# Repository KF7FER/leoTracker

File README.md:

leoTracker
==========

Small AVR-based standalone APRS Tracker for [Trackuino](http://www.trackuino.org/)

This board was designed to be fairly inexpensive (BOM is $50 depending upon power source), small (1.25"x2.85"), light (under 17g depending upon configuration), and offer some features typically not available on other trackers.  

A ready to fly leoTracker (sans antenna) often weighs less than the power supply needed for other commercial APRS trackers.

Features include:

- ublox MAX-7/8 GPS w/ chip antenna
- Multiple Power options including boost converter (2xAA operation)
- Atmel (AVR) 32u4 Processor (same as in the Arduino Leonardo - hence the "leo")
- On-board USB for easy firmware updates
- microSD socket for data logging/board configuration
- DS18b20 temperature sensor (and connection for off-board sensor)
- NiceRF SA818 2m radio module (frequency agile; multiple power levels)

The leoTracker ONE
------------------

This is a test version of the leoTracker with an on-board single "AA" battery.  Testing has shown that despite running the SA818 just outside of the published specifications, the leoTracker will function correctly for 11+ hours.  It also has a few changes to support soldering the antenna directly to the PCB to reduce overall payload weight.

Status
--------

I just submitted the Revision "J" boards to fabrication and will post the results here.  The primary changes were a slightly changed footprint for the SA818; I changed the crystal footprint to match the part specified in the BOM (which actually has better low-temperature performance); and I cleaned up the silkscreen for fabrication.

Since those are very minor changes I don't expect any problems but I'll update this as soon as I get the boards back in my hands.

Firmware
--------
The firmware is available at [github.com/KF7FER/trackuino](https://github.com/KF7FER/trackuino). It is modified from the [John Boiles](https://github.com/johnboiles/trackuino) port in order to support the different pin mappings used on the leoTracker (as well as support of additional hardware).  This is, of course, based on EA5HAV's original [Trackuino](https://code.google.com/p/trackuino/)

Changes to the firmware include:

- Support for the ublox MAX-6/7/8 (switch to flight mode; use low power mode when possible)
- Support for the on-board microSD card (still a work in progress)
- Support for the Dallas DS18b20 temperature sensors (two are supported)
- Added support for the NiceRF SA818 radio module

I/O Pin Usage
--------
Here is a document listing I/O pin usage for the different leoTracker versions

Powering the leoTracker
--------

The board may be powered by the following methods:

- Add-on TI TPS61202 Boost converter ([Pololu U1V10F3](http://www.pololu.com/product/2563)) on JP1
- 2xAA Boost converter board (files available w/ leoTracker)
- 3.3v LDO board (this is for vehicle/aircraft use) for 5-20v power sources
- A LiPoly/Solar board is currently under development

Bill of Materials
-----------------

The Bill of Materials is a bit out of date but should be fairly close

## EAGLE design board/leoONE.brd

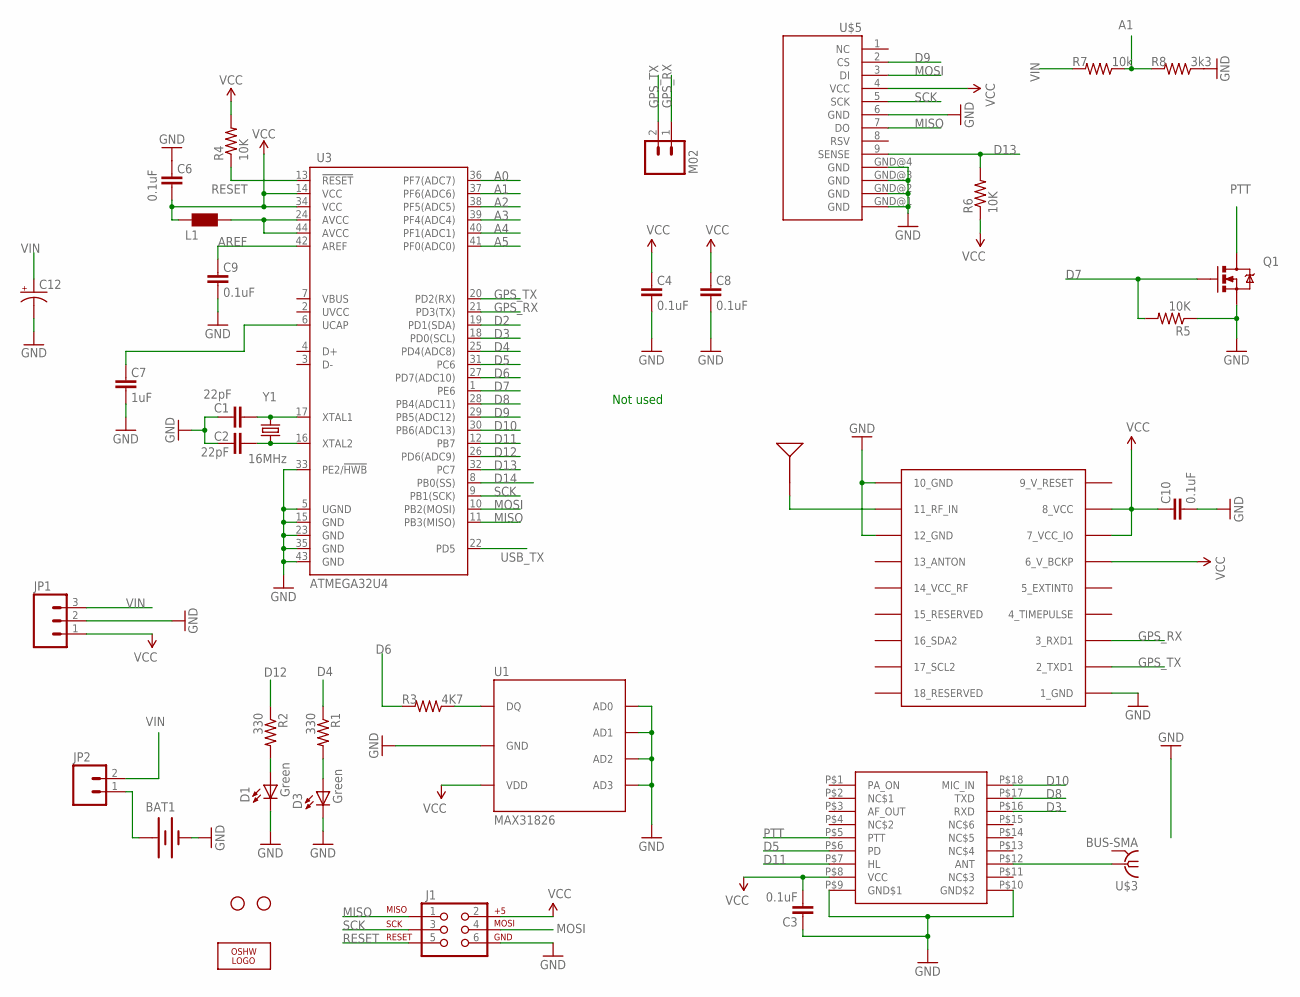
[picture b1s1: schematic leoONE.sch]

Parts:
BAT1: BATTERYAA; BATTERY-AA
C1, C2: 22pF; 0805
C3, C6, C9, C10: 0.1uF; 0805
C4, C8: 0.1uF; 0402-CAP
C7: 1uF; 0805
C12: CPOL-US153CLV-0405; 153CLV-0405
D1, D3: Green; LED-0603
J1: AVR_SPI_PRG_6PTH; 2X3
JP1: M03LOCK; 1X03_LOCK
JP2: M02LOCK; 1X02_LOCK
L1: MH2029-300Y; 0805
LOGO1: OSHW_LOGO_8MILX0200-NT; OSHW_8X200_NOTEXT
Q1: MOSFET-NCHANNELSMD; SOT23-3
R1, R2: 330; 0805
R3: 4K7; 0805
R4, R5, R6: 10K; 0805
R7: 10k; 0805
R8: 3k3; 0805
STANDOFF1, STANDOFF2: STAND-OFFTIGHT; STAND-OFF-TIGHT
U1: MAX31826; UMAX8
U3: ATMEGA32U4; SPARKFUN-DIGITALIC_TQFP44
U$1: ANTENNA2SMD6; ANTENNA-CHIP6
U$2: UBLOX_MAX
U$3: BUS-SMA
U$5: MICROSD_PI; MICROSD_PP
U$7: SA818
U$8: M02
Y1: 16MHz; ABRACON_ABM3_CRYSTAL

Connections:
9_V_RESET: U$2.9_V_RESET
A0: U3.36 (PF7(ADC7))
A1: R7.1, R8.2, U3.37 (PF6(ADC6))
A2: U3.38 (PF5(ADC5))
A3: U3.39 (PF4(ADC4))
A4: U3.40 (PF1(ADC1))
A5: U3.41 (PF0(ADC0))
AREF: C9.2, U3.42 (AREF)
D2: U3.19 (PD1(SDA))
D3: U3.18 (PD0(SCL)), U$7.P$16 (RXD)
D4: R1.1, U3.25 (PD4(ADC8))
D5: U3.31 (PC6), U$7.P$6 (PD)
D6: R3.2, U3.27 (PD7(ADC10))
D7: Q1.1 (G), R5.2, U3.1 (PE6)
D8: U3.28 (PB4(ADC11)), U$7.P$17 (TXD)
D9: U3.29 (PB5(ADC12)), U$5.2 (CS)
D10: U3.30 (PB6(ADC13)), U$7.P$18 (MIC_IN)
D11: U3.12 (PB7), U$7.P$7 (HL)
D12: R2.1, U3.26 (PD6(ADC9))
D13: R6.2, U3.32 (PC7), U$5.9 (SENSE)
D14: U3.8 (PB0(SS))
GND: BAT1.GND@1 (-), C1.2, C2.2, C3.2, C4.1, C6.2, C7.1, C8.1, C9.1, C10.1, C12.-, D1.C, D3.C, J1.6, JP1.2, Q1.2 (S), R5.1, R8.1, U1.4 (GND), U1.5 (AD0), U1.6 (AD1), U1.7 (AD2), U1.8 (AD3), U3.5 (UGND), U3.15 (GND), U3.23 (GND), U3.33 (PE2/!HWB), U3.35 (GND), U3.43 (GND), U$2.1_GND, U$2.10_GND, U$2.12_GND, U$3.2 (GND), U$3.3 (GND), U$3.4 (GND), U$3.5 (GND), U$5.6 (GND), U$5.GND@1 (GND), U$5.GND@2 (GND), U$5.GND@3 (GND), U$5.GND@4 (GND), U$7.P$9 (GND$1), U$7.P$10 (GND$2)
GPS_RX: U3.21 (PD3(TX)), U$2.3_RXD1, U$8.1
GPS_TX: U3.20 (PD2(RX)), U$2.2_TXD1, U$8.2
MISO: J1.1, U3.11 (PB3(MISO)), U$5.7 (DO)
MOSI: J1.4, U3.10 (PB2(MOSI)), U$5.3 (DI)
unnamed: C2.1, U3.16 (XTAL2), Y1.P$1 (1)
unnamed: C1.1, U3.17 (XTAL1), Y1.P$2 (2)
unnamed: R3.1, U1.2 (DQ)
unnamed: C7.2, U3.6 (UCAP)
unnamed: D3.A, R1.2
unnamed: BAT1.PWR@1 (+), JP2.1
unnamed: D1.A, R2.2
unnamed: U$1.1, U$2.11_RF_IN
unnamed: L1.2, U3.24 (AVCC), U3.44 (AVCC)
unnamed: U$3.1, U$7.P$12 (ANT)
PTT: Q1.3 (D), U$7.P$5 (PTT)
RESET: J1.5, R4.1, U3.13 (!RESET)
SCK: J1.3, U3.9 (PB1(SCK)), U$5.5 (SCK)
USB_TX: U3.22 (PD5)
VCC: C3.1, C4.2, C6.1, C8.2, C10.2, J1.2, JP1.1, L1.1, R4.2, R6.1, U1.1 (VDD), U3.14 (VCC), U3.34 (VCC), U$2.6_V_BCKP, U$2.7_VCC_IO, U$2.8_VCC, U$5.4 (VCC), U$7.P$8 (VCC)
VIN: C12.+, JP1.3, JP2.2, R7.2

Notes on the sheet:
Not used

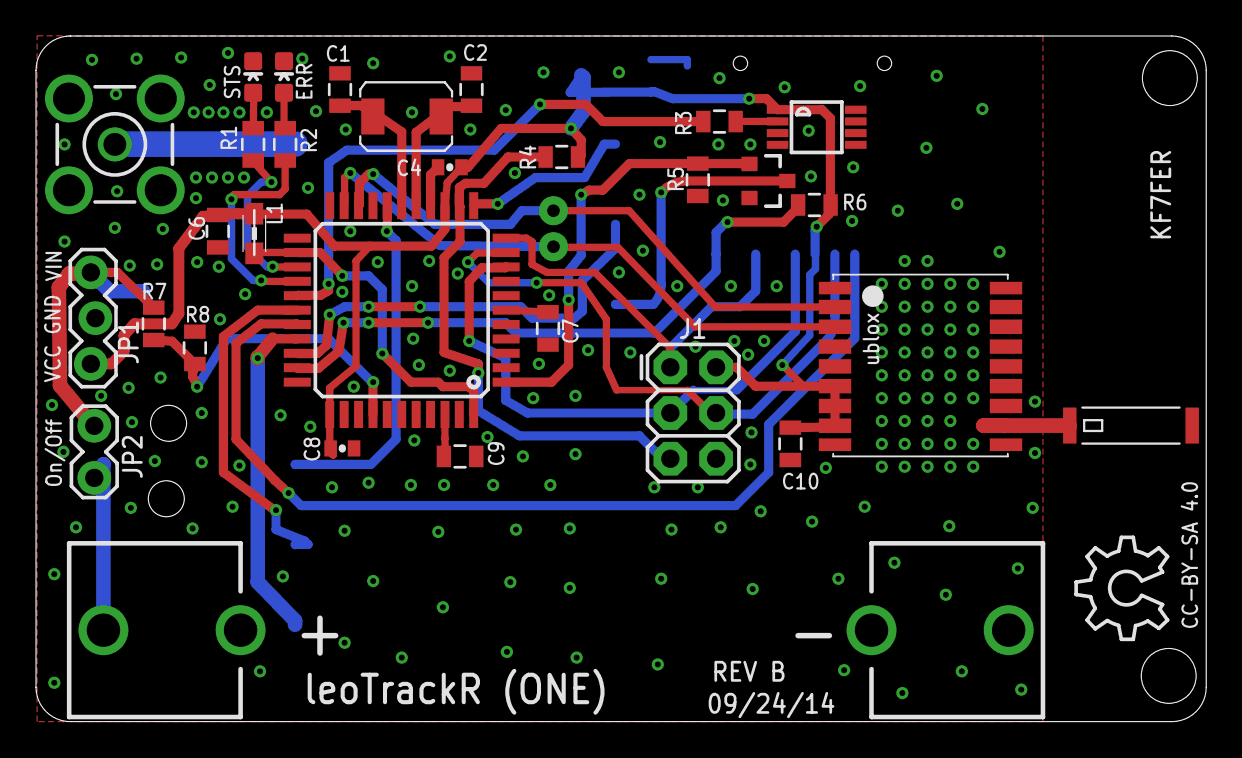
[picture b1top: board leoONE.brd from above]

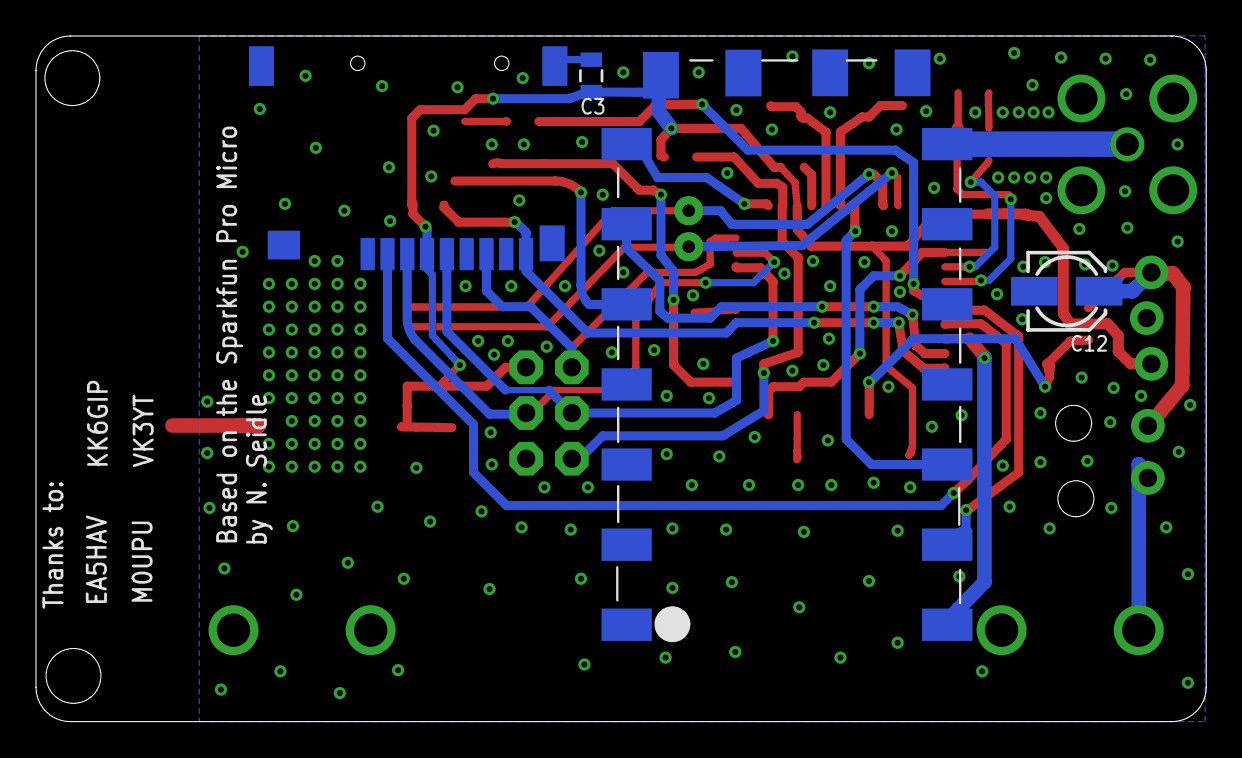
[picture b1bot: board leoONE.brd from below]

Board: 2 copper layers, 65.0 x 38.1 mm, 38 parts (4 on the bottom side), 33 nets.

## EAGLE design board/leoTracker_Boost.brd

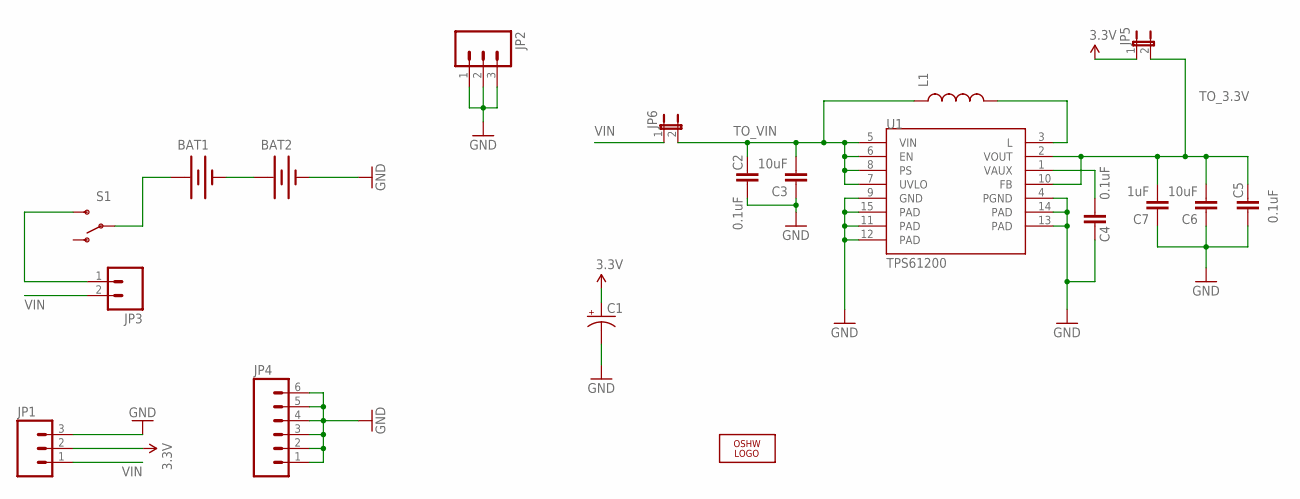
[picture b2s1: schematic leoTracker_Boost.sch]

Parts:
BAT1, BAT2: BATTERYAA; BATTERY-AA
C1: CAP_POL1206; EIA3216
C2, C4, C5: 0.1uF; 0805
C3, C6: 10uF; 0805
C7: 1uF; 0805
JP1, JP2: M03LOCK; 1X03_LOCK
JP3: M02LOCK; 1X02_LOCK
JP4: M06LOCK; 1X06_LOCK
JP5, JP6: JUMPER-2SMD-NC; SJ_2S
L1: INDUCTOR.; CDRH2D09
LOGO2: OSHW_LOGO_6MILX0100-NT; OSHW_6X100_NOTEXT
S1: SWITCH-SPDTPTH; SWITCH-SPDT
U1: TPS61200; QFN-10_PAD

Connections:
3.3V: C1.A (+), JP1.2, JP5.1
GND: BAT2.GND@1 (-), C1.C (-), C2.2, C3.1, C4.1, C5.2, C6.1, C7.1, JP1.3, JP2.1, JP2.2, JP2.3, JP4.1, JP4.2, JP4.3, JP4.4, JP4.5, JP4.6, U1.4 (PGND), U1.9 (GND), U1.11 (PAD), U1.12 (PAD), U1.13 (PAD), U1.14 (PAD), U1.15 (PAD)
unnamed: L1.P$2 (2), U1.3 (L)
unnamed: JP3.1, S1.3 (S)
unnamed: BAT1.GND@1 (-), BAT2.PWR@1 (+)
unnamed: BAT1.PWR@1 (+), S1.2
unnamed: C4.2, U1.1 (VAUX)
TO_3.3V: C5.1, C6.2, C7.2, JP5.2, U1.2 (VOUT), U1.10 (FB)
TO_VIN: C2.1, C3.2, JP6.2, L1.P$1 (1), U1.5 (VIN), U1.6 (EN), U1.7 (UVLO), U1.8 (PS)
VIN: JP1.1, JP3.2, JP6.1

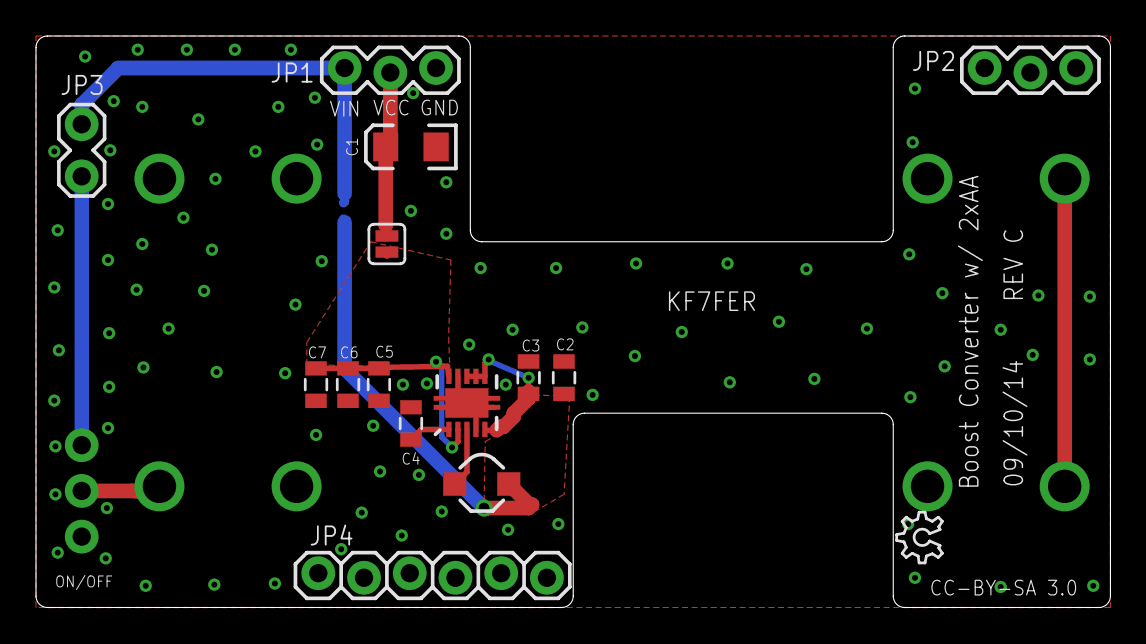
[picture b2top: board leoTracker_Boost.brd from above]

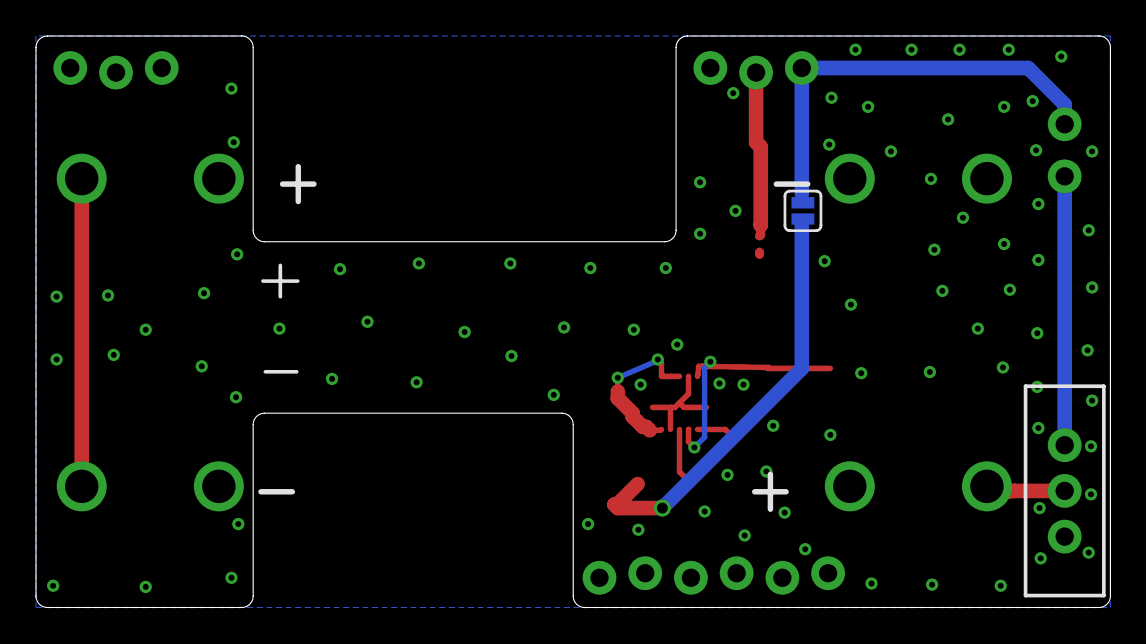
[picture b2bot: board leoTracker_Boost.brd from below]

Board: 2 copper layers, 59.7 x 31.8 mm, 19 parts (4 on the bottom side), 10 nets.

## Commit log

2014-09-13 Initial import w/ current Eagle files; started editing Readme.md
2014-09-13 Initial check-in of current files
    Started w/ Rev "G" board and "C" boost boards as submitted to OSHPark.
2014-09-13 Added details about board/firmware
2014-09-13 Corrected typo
2014-09-13 Added BOM information
2014-09-13 Corrected bad link
2014-09-13 The URL corrections continue
2014-09-13 minor wording cleanup
2014-09-13 Added power info
2014-09-13 Gimme mo' URL correction for $100 Jim...
2014-09-13 More cleanup
2014-09-13 Added details for Pololu boost converter
2014-09-14 Added corrected Solar details
2014-09-14 Just trying to be kind...
2014-09-14 Added a bit of whitespace
2014-09-14 A little more cleanup (OCD much?)
2014-09-14 Language cleanup
2014-09-14 Added license file
2014-09-15 Added new pics of Revision G
2014-09-15 added Eagle library for SA818 radio module
2014-09-15 Initial check-in
2014-09-15 Added pin definitions; status section
2014-09-15 Language clarification
2014-09-15 Mo' language cleanup
2014-09-16 Added availability info
2014-09-20 Minor correction to pad placement after latest board run
2014-09-20 Status update
2014-09-27 Latest version: Used new SA818 footprint; changed crystal; cleaned up silkscreen for fabrication
2014-09-27 Initial creation; untested
2014-09-27 Updated status
2014-09-29 Added pics of new boards
2014-09-29 Corrected link

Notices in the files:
board/leoONE.brd:
CC-BY-SA 4.0
board/leoTracker_Boost.brd:
CC-BY-SA 3.0
parts and their libraries:
SparkFun-Passives: Licensing: Creative Commons ShareAlike 4.0 International - https://creativecommons.org/licenses/by-sa/4.0
SparkFun-PowerIC: Licensing: CC v3.0 Share-Alike You are welcome to use this library for commercial purposes.
